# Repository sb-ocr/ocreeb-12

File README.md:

# Ocreeb12

Watch the build video ↓

This is a 12 key macro keypad with 2 rotary encoders, custom keycaps and under-glow RGB. 
Ocreeb is running KMK firmware on the Adafruit KB2040.

Order the PCB: [pcbway.com](https://www.pcbway.com/project/shareproject/DIY_Mechanical_Macro_Keypad_Ocreeb_24300065.html)

Build instructions: [instructables.com](https://www.instructables.com/DIY-Mechanical-Macro-Keypad-Ocreeb/)

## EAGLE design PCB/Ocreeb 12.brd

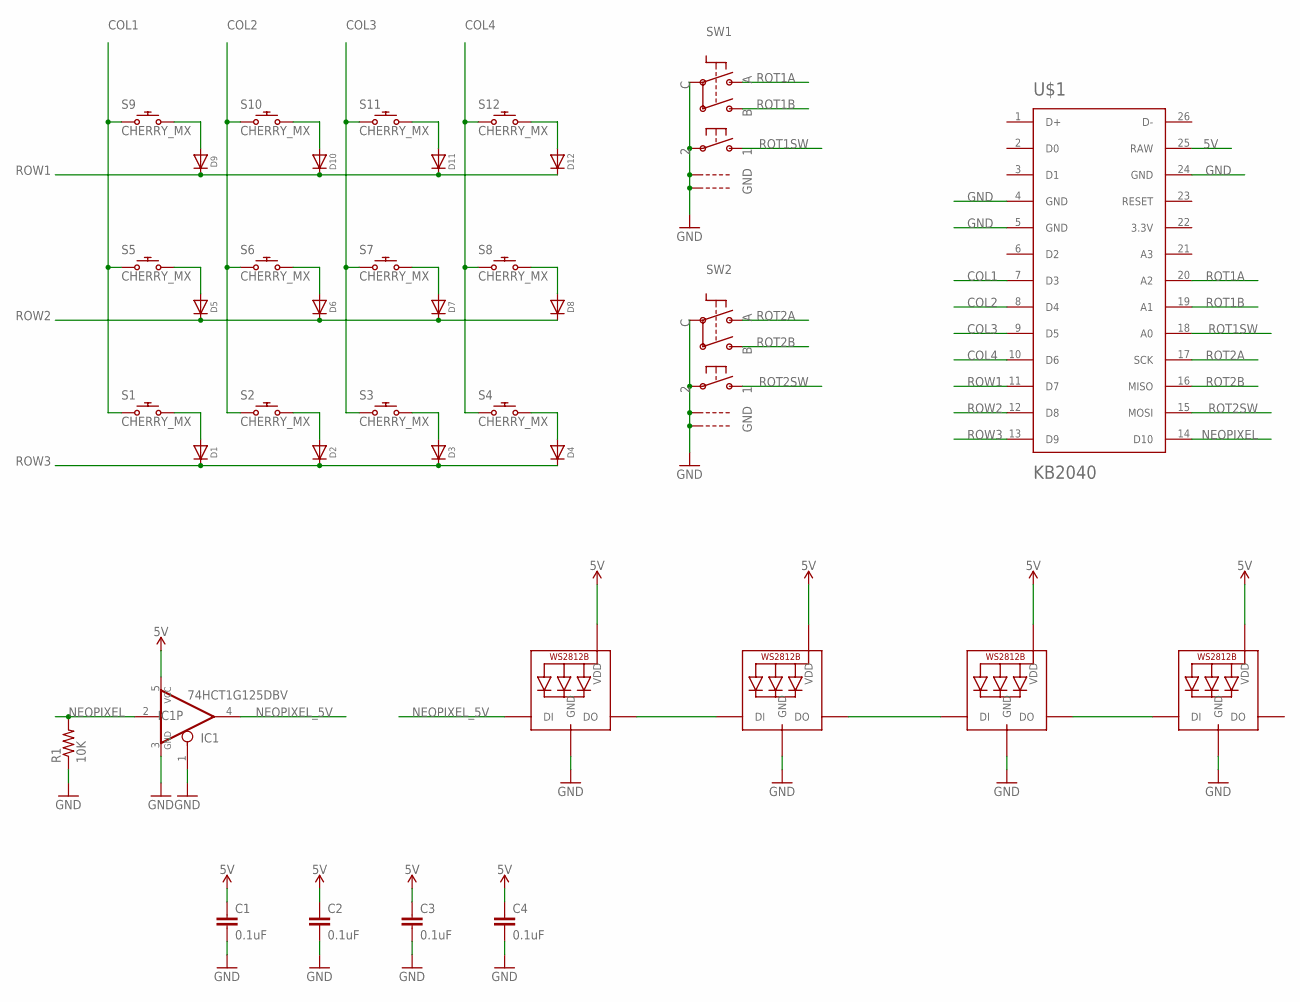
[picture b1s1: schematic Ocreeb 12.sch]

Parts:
C1, C2, C3, C4: 0.1uF; 0603
D1, D2, D3, D4, D5, D6, D7, D8, D9, D10, D11, D12: MICROBUILDER_DIODESOD-123; MICROBUILDER_SOD-123
IC1: 74HCT1G125DBV; SOT23-5
LED1, LED2, LED3, LED4: WS2812B5050; WS2812B
R1: 10K; R0805
S1, S2, S3, S4, S5, S6, S7, S8, S9, S10, S11, S12: CHERRY_MX
SW1, SW2: ADAFRUIT_ELECTROMECH_ENCODER_PLUS_SWITCH_BOURNS_P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; ADAFRUIT_ELECTROMECH_PEC11+SWITCH
U$1: KB2040; KB2040_SMD

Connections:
5V: C1.1, C2.1, C3.1, C4.1, IC1.5 (VCC), LED1.1-VDD (VDD), LED2.1-VDD (VDD), LED3.1-VDD (VDD), LED4.1-VDD (VDD), U$1.25 (RAW)
COL1: S1.S1 (1), S5.S1 (1), S9.S1 (1), U$1.7 (D3)
COL2: S2.S1 (1), S6.S1 (1), S10.S1 (1), U$1.8 (D4)
COL3: S3.S1 (1), S7.S1 (1), S11.S1 (1), U$1.9 (D5)
COL4: S4.S1 (1), S8.S1 (1), S12.S1 (1), U$1.10 (D6)
GND: C1.2, C2.2, C3.2, C4.2, IC1.1 (OE), IC1.3 (GND), LED1.3-GND (GND), LED2.3-GND (GND), LED3.3-GND (GND), LED4.3-GND (GND), R1.1, SW1.P$2, SW1.P$C, SW1.P$GND1, SW1.P$GND2, SW2.P$2, SW2.P$C, SW2.P$GND1, SW2.P$GND2, U$1.4 (GND), U$1.5 (GND), U$1.24 (GND)
unnamed: LED1.2-DOUT (DO), LED2.4-DIN (DI)
unnamed: LED2.2-DOUT (DO), LED3.4-DIN (DI)
unnamed: LED3.2-DOUT (DO), LED4.4-DIN (DI)
unnamed: D5.A, S5.S2 (2)
unnamed: D6.A, S6.S2 (2)
unnamed: D8.A, S8.S2 (2)
unnamed: D7.A, S7.S2 (2)
unnamed: D2.A, S2.S2 (2)
unnamed: D3.A, S3.S2 (2)
unnamed: D1.A, S1.S2 (2)
unnamed: D4.A, S4.S2 (2)
unnamed: D10.A, S10.S2 (2)
unnamed: D12.A, S12.S2 (2)
unnamed: D11.A, S11.S2 (2)
unnamed: D9.A, S9.S2 (2)
NEOPIXEL: IC1.2 (I), R1.2, U$1.14 (D10)
NEOPIXEL_5V: IC1.4 (O), LED1.4-DIN (DI)
ROT1A: SW1.P$A, U$1.20 (A2)
ROT1B: SW1.P$B, U$1.19 (A1)
ROT1SW: SW1.P$1, U$1.18 (A0)
ROT2A: SW2.P$A, U$1.17 (SCK)
ROT2B: SW2.P$B, U$1.16 (MISO)
ROT2SW: SW2.P$1, U$1.15 (MOSI)
ROW1: D9.C, D10.C, D11.C, D12.C, U$1.11 (D7)
ROW2: D5.C, D6.C, D7.C, D8.C, U$1.12 (D8)
ROW3: D1.C, D2.C, D3.C, D4.C, U$1.13 (D9)

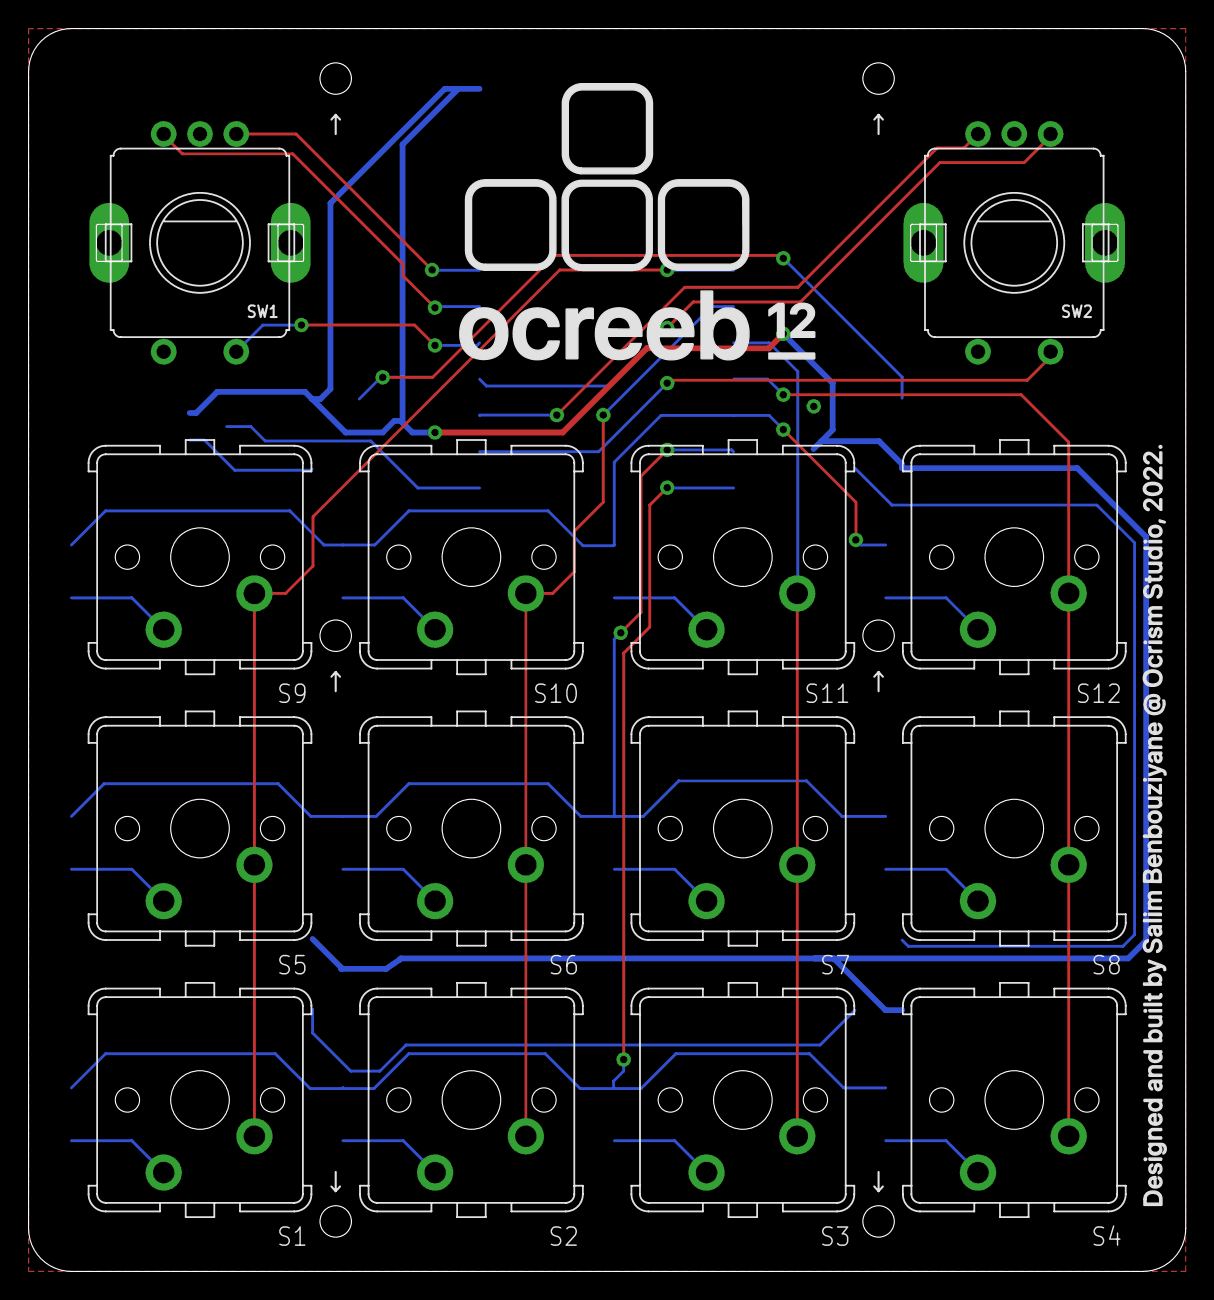
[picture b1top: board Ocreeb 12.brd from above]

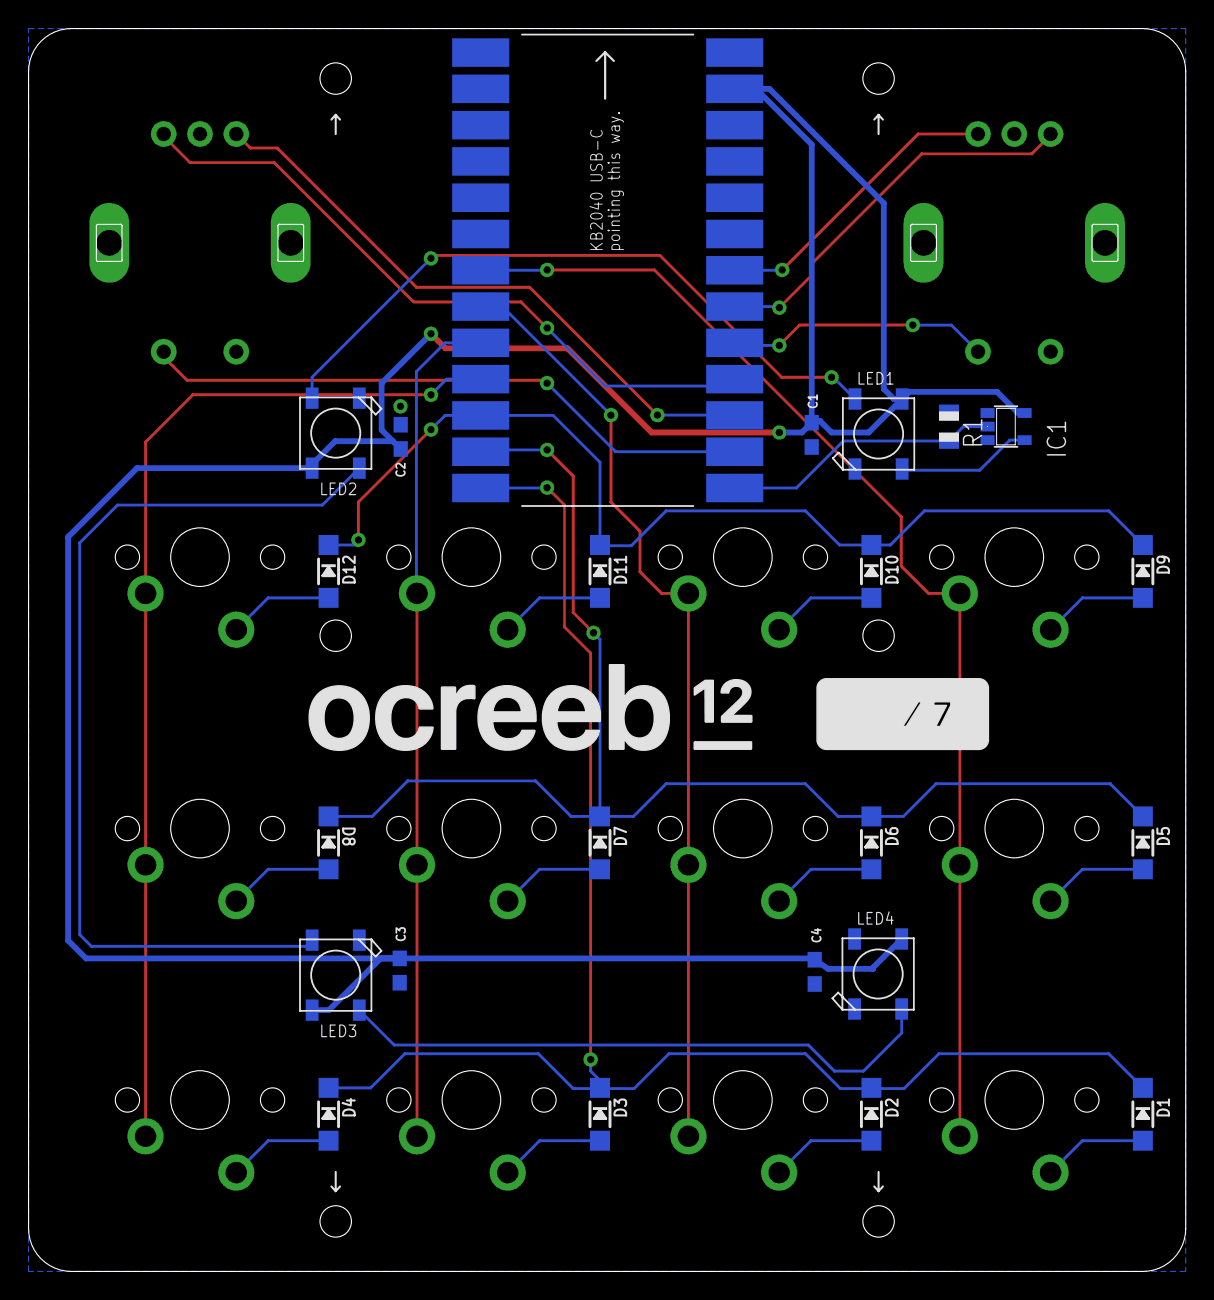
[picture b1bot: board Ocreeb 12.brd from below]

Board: 2 copper layers, 81.0 x 87.0 mm, 37 parts (23 on the bottom side), 32 nets.

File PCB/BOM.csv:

Qty,Value,Digikey,Device,Package,Parts,Description,
2,,PEC11R-4215F-S0024-ND,ELECTROMECH_ENCODER_PLUS_SWITCH_BOURNS_PEC11,ELECTROMECH_PEC11+SWITCH,"SW1, SW2",Rotary Encoder with Built-In Switch,
12,,1655-1360-1-ND,DIODESOD-123,MICROBUILDER_SOD-123,"D1, D2, D3, D4, D5, D6, D7, D8, D9, D10, D11, D12",Diode,
4,0.1uF,276-CL10B104KB8NNNLCT-ND,0.1UF-0603-25V-(+80/-20%),603,"C1, C2, C3, C4",0.1µF ceramic capacitors,
1,10K,RMCF0805JG10K0CT-ND,R-US_R0805,R0805,R1,"RESISTOR, American symbol",
1,74HCT1G125DBV,296-49526-1-ND,74AHC1G125DBV,SOT23-5,IC1,Single Bus Buffer Gate with 3-State Output,
12,CHERRY_MX,1528-4952-ND,CHERRY_MX,CHERRY_MX,"S1, S2, S3, S4, S5, S6, S7, S8, S9, S10, S11, S12",Cherry keymodule MX,
1,KB2040,1528-5302-ND,KB2040,KB2040_SMD,U1,Adafruit KB2040,
4,WS2812B5050,1528-1104-ND,WS2812B5050,WS2812B,"LED1, LED2, LED3, LED4",Neopixels,

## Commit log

2022-09-10 removed .DS_store
2022-09-10 License
2022-09-26 Youtube Video Link
2022-09-27 Build Instructable and PCB Way link
2022-10-20 bugfix encoder
    I've got the problem, that i could use just one binding for both encoder-buttons.
    Encoders-Buttons got the same id. This commit will fix the problem
2022-11-11 Libraries Export
2022-11-15 Peg client compatible firmware
2022-11-15 Getting Started
    A user guide to customize Ocreeb 12 using the Peg Flashing Software
2022-11-16 RGB encoder extension
2022-11-16 Peg user guide images
2022-11-16 Images sizes
2022-11-16 Rename Getting Started.md to README.md
2022-11-16 SVG text outlined
2023-07-15 Restore RGB color after reboot
2023-08-11 QMK and VIA support

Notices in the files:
parts and their libraries:
SparkFun-Capacitors: Licensing: Creative Commons ShareAlike 4.0 International - https://creativecommons.org/licenses/by-sa/4.0
